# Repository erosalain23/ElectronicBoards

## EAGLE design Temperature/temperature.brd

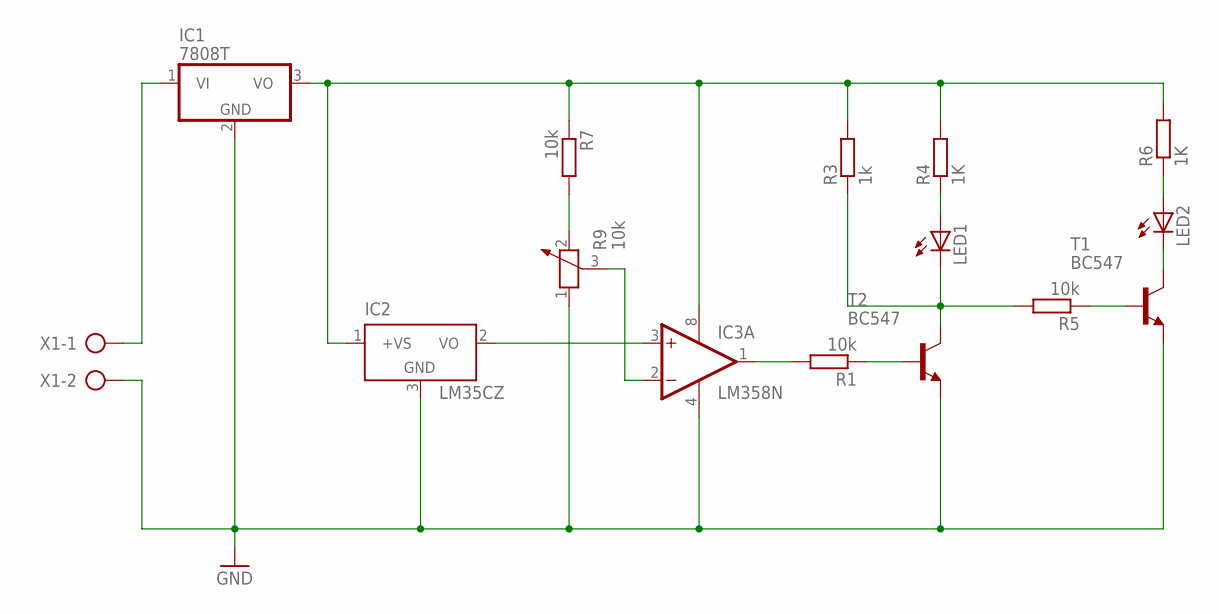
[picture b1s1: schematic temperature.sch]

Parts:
IC1: 7808T; TO220H
IC2: LM35CZ; TO92
IC3: LM358N; DIL08
LED1, LED2: LED5MM
R1, R5, R7: 10k; 0204/7
R3: 1k; 0204/7
R4, R6: 1K; 0204/7
R9: 10k; PT-10
T1, T2: BC547; TO92
X1: AK300/2

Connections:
GND: IC1.2 (GND), IC2.3 (GND), IC3.4 (V-), R9.1, T1.1 (E), T2.1 (E), X1.2
unnamed: IC1.1 (VI), X1.1
unnamed: IC1.3 (VO), IC2.1 (+VS), IC3.8 (V+), R3.2, R4.2, R6.2, R7.1
unnamed: R7.2, R9.2
unnamed: IC2.2 (VO), IC3.3 (+IN)
unnamed: IC3.2 (-IN), R9.3
unnamed: IC3.1 (OUT), R1.2
unnamed: R1.1, T2.2 (B)
unnamed: LED1.K (C), R3.1, R5.2, T2.3 (C)
unnamed: LED1.A, R4.1
unnamed: LED2.K (C), T1.3 (C)
unnamed: LED2.A, R6.1
unnamed: R5.1, T1.2 (B)

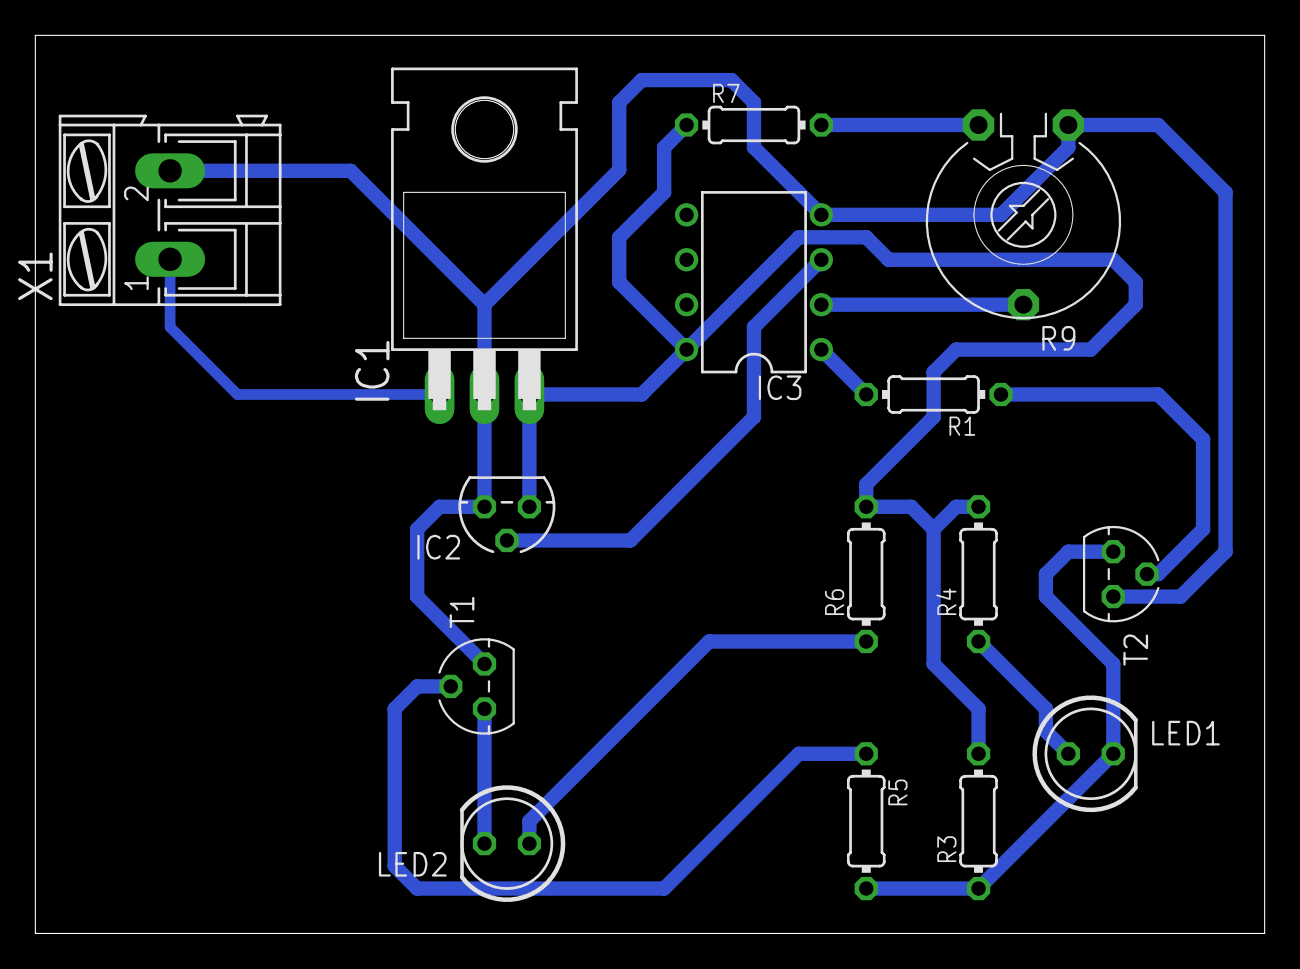
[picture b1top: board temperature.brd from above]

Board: 2 copper layers, 69.5 x 50.8 mm, 15 parts (0 on the bottom side), 13 nets.

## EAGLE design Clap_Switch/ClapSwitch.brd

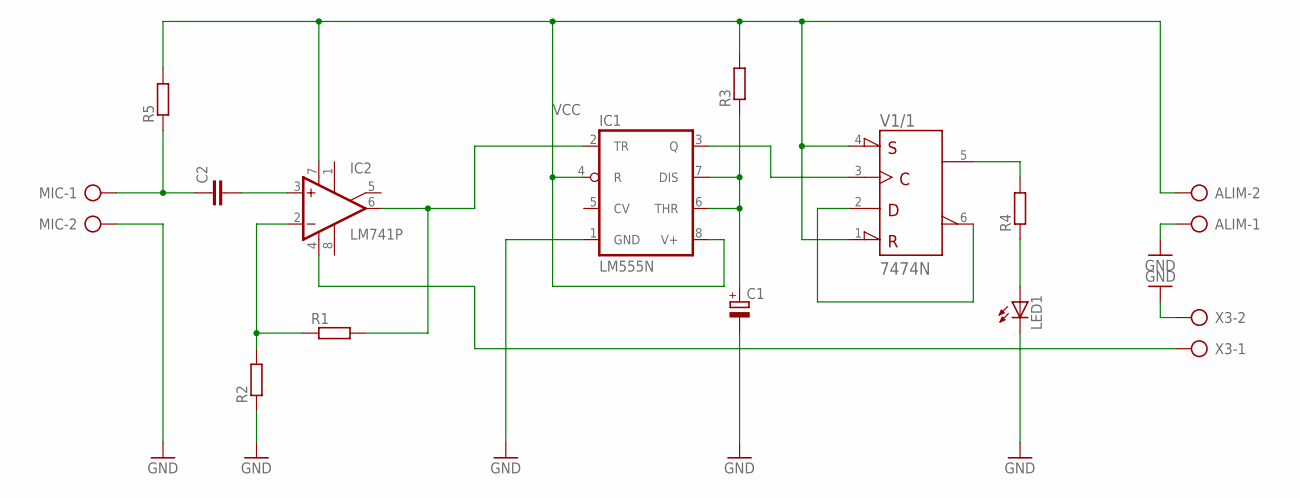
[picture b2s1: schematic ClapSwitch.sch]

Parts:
ALIM: AK300/2
C1: CPOL-EUE5-8.5; E5-8,5
C2: C-EU050-030X075; C050-030X075
IC1: LM555N; DIL08
IC2: LM741P; DIL08
LED1: LEDLZR181; LZR181
MIC: AK300/2
R1, R2, R3, R4, R5: R-EU_0204/7; 0204/7
V1: 7474N; DIL14
X3: AK300/2

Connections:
+UB: V1.14 (+UB)
-UB: V1.7 (-UB)
GND: ALIM.1, C1.-, IC1.1 (GND), LED1.K (C), MIC.2, R2.1, X3.2
unnamed: IC1.3 (Q), V1.3 (CLK)
unnamed: IC2.4 (V-), X3.1
unnamed: V1.2 (D), V1.6 (!Q)
unnamed: R4.2, V1.5 (Q)
unnamed: C1.+, IC1.6 (THR), IC1.7 (DIS), R3.1
unnamed: LED1.A, R4.1
unnamed: C2.1, MIC.1, R5.1
unnamed: IC1.2 (TR), IC2.6 (OUT), R1.2
unnamed: IC2.2 (-IN), R1.1, R2.2
unnamed: C2.2, IC2.3 (+IN)
VCC: ALIM.2, IC1.4 (R), IC1.8 (V+), IC2.7 (V+), R3.2, R5.2, V1.1 (!CLR), V1.4 (!PRE)

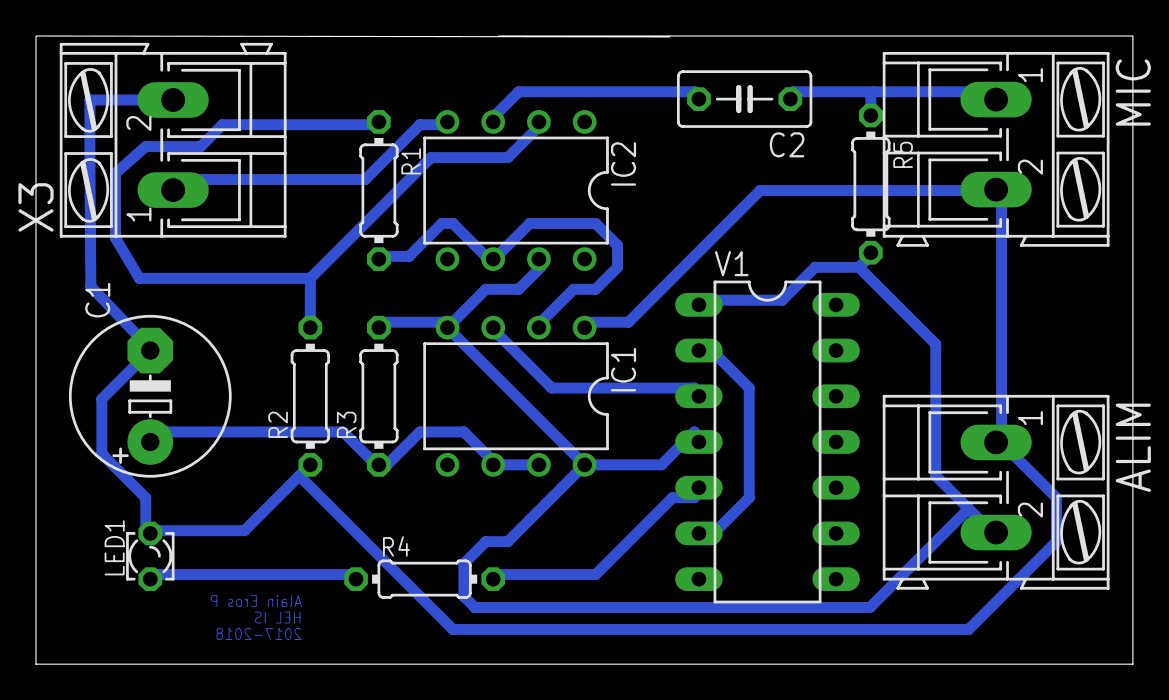
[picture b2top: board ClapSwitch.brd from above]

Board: 2 copper layers, 60.9 x 34.9 mm, 14 parts (0 on the bottom side), 12 nets.

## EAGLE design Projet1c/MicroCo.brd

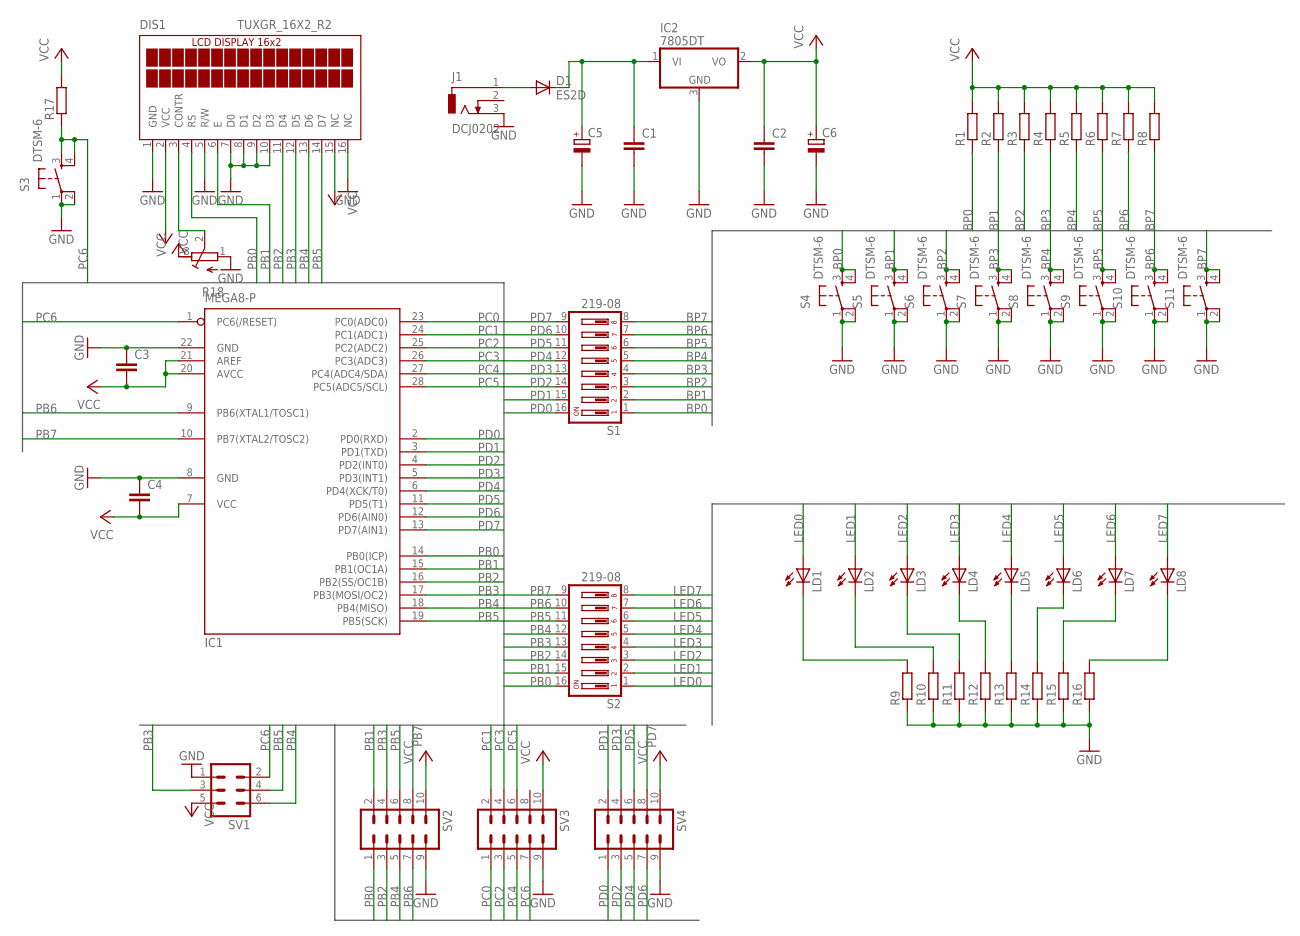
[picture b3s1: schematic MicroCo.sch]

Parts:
C1, C2, C3, C4: C-EUC1206; C1206
C5: CPOL-EU153CLV-1010; 153CLV-1010
C6: CPOL-EU153CLV-0605; 153CLV-0605
D1: ES2D; SMB
DIS1: TUXGR_16X2_R2
IC1: MEGA8-P; DIL28-3
IC2: 7805DT; TO252
J1: DCJ0202
LD1, LD2, LD3, LD4, LD5, LD6, LD7, LD8: LEDCHIPLED_1206; CHIPLED_1206
R1, R2, R3, R4, R5, R6, R7, R8, R9, R10, R11, R12, R13, R14, R15, R16, R17: R-EU_M1206; M1206
R18: R-TRIMM4G/J; RTRIM4G/J
S1, S2: 219-08; CTS-219-08
S3, S4, S5, S6, S7, S8, S9, S10, S11: DTSM-6
SV1: ML6
SV2, SV3, SV4: MA05-2

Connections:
BP0: R1.1, S1.1, S4.3, S4.4
BP1: R2.1, S1.2, S5.3, S5.4
BP2: R3.1, S1.3, S6.3, S6.4
BP3: R4.1, S1.4, S7.3, S7.4
BP4: R5.1, S1.5, S8.3, S8.4
BP5: R6.1, S1.6, S9.3, S9.4
BP6: R7.1, S1.7, S10.3, S10.4
BP7: R8.1, S1.8, S11.3, S11.4
GND: C1.2, C2.2, C3.1, C4.1, C5.-, C6.-, DIS1.1 (GND), DIS1.5 (R/W), DIS1.7 (D0), DIS1.8 (D1), DIS1.9 (D2), DIS1.10 (D3), DIS1.16 (NC), IC1.8 (GND), IC1.22 (GND), IC2.3 (GND), J1.3, R9.1, R10.1, R11.1, R12.1, R13.1, R14.1, R15.1, R16.1, R18.1 (A), S3.1, S3.2, S4.1, S4.2, S5.1, S5.2, S6.1, S6.2, S7.1, S7.2, S8.1, S8.2, S9.1, S9.2, S10.1, S10.2, S11.1, S11.2, SV1.1, SV2.9, SV3.9, SV4.9
LED0: LD1.A, S2.1
LED1: LD2.A, S2.2
LED2: LD3.A, S2.3
LED3: LD4.A, S2.4
LED4: LD5.A, S2.5
LED5: LD6.A, S2.6
LED6: LD7.A, S2.7
LED7: LD8.A, S2.8
unnamed: DIS1.3 (CONTR), R18.2 (S)
unnamed: D1.A, J1.1
unnamed: C1.1, C5.+, D1.C, IC2.1 (VI)
unnamed: LD1.C, R9.2
unnamed: LD2.C, R10.2
unnamed: LD3.C, R11.2
unnamed: LD4.C, R12.2
unnamed: LD5.C, R13.2
unnamed: LD6.C, R14.2
unnamed: LD7.C, R15.2
unnamed: LD8.C, R16.2
PB0: DIS1.4 (RS), IC1.14 (PB0(ICP)), S2.16, SV2.1
PB1: DIS1.6 (E), IC1.15 (PB1(OC1A)), S2.15, SV2.2
PB2: DIS1.11 (D4), IC1.16 (PB2(SS/OC1B)), S2.14, SV2.3
PB3: DIS1.12 (D5), IC1.17 (PB3(MOSI/OC2)), S2.13, SV1.3, SV2.4
PB4: DIS1.13 (D6), IC1.18 (PB4(MISO)), S2.12, SV1.6, SV2.5
PB5: DIS1.14 (D7), IC1.19 (PB5(SCK)), S2.11, SV1.4, SV2.6
PB6: IC1.9 (PB6(XTAL1/TOSC1)), S2.10, SV2.7
PB7: IC1.10 (PB7(XTAL2/TOSC2)), S2.9, SV2.8
PC0: IC1.23 (PC0(ADC0)), SV3.1
PC1: IC1.24 (PC1(ADC1)), SV3.2
PC2: IC1.25 (PC2(ADC2)), SV3.3
PC3: IC1.26 (PC3(ADC3)), SV3.4
PC4: IC1.27 (PC4(ADC4/SDA)), SV3.5
PC5: IC1.28 (PC5(ADC5/SCL)), SV3.6
PC6: IC1.1 (PC6(/RESET)), R17.1, S3.3, S3.4, SV1.2, SV3.7
PD0: IC1.2 (PD0(RXD)), S1.16, SV4.1
PD1: IC1.3 (PD1(TXD)), S1.15, SV4.2
PD2: IC1.4 (PD2(INT0)), S1.14, SV4.3
PD3: IC1.5 (PD3(INT1)), S1.13, SV4.4
PD4: IC1.6 (PD4(XCK/T0)), S1.12, SV4.5
PD5: IC1.11 (PD5(T1)), S1.11, SV4.6
PD6: IC1.12 (PD6(AIN0)), S1.10, SV4.7
PD7: IC1.13 (PD7(AIN1)), S1.9, SV4.8
VCC: C2.1, C3.2, C4.2, C6.+, DIS1.2 (VCC), DIS1.15 (NC), IC1.7 (VCC), IC1.20 (AVCC), IC1.21 (AREF), IC2.2 (VO), R1.2, R2.2, R3.2, R4.2, R5.2, R6.2, R7.2, R8.2, R17.2, R18.3 (E), SV1.5, SV2.10, SV3.10, SV4.10

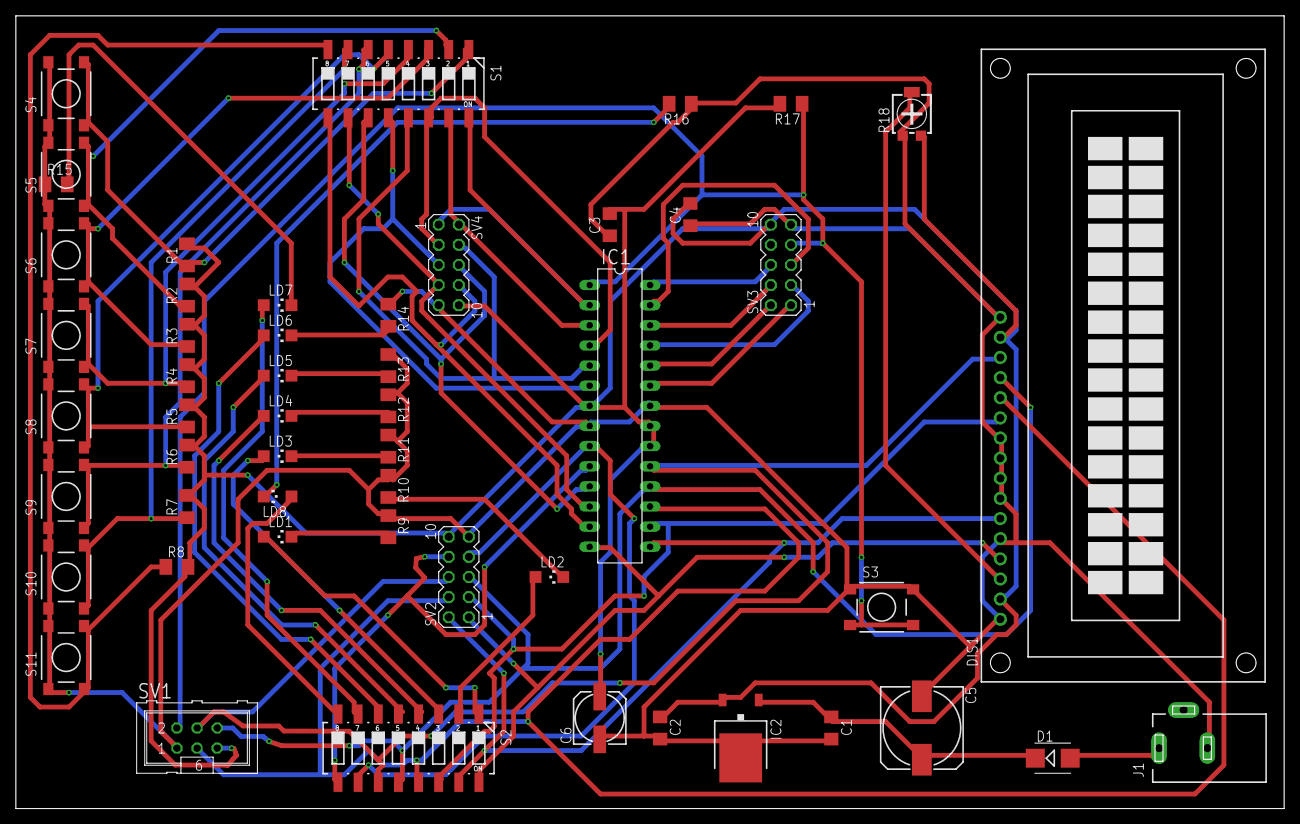
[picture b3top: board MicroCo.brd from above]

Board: 2 copper layers, 160.0 x 100.0 mm, 52 parts (0 on the bottom side), 52 nets.

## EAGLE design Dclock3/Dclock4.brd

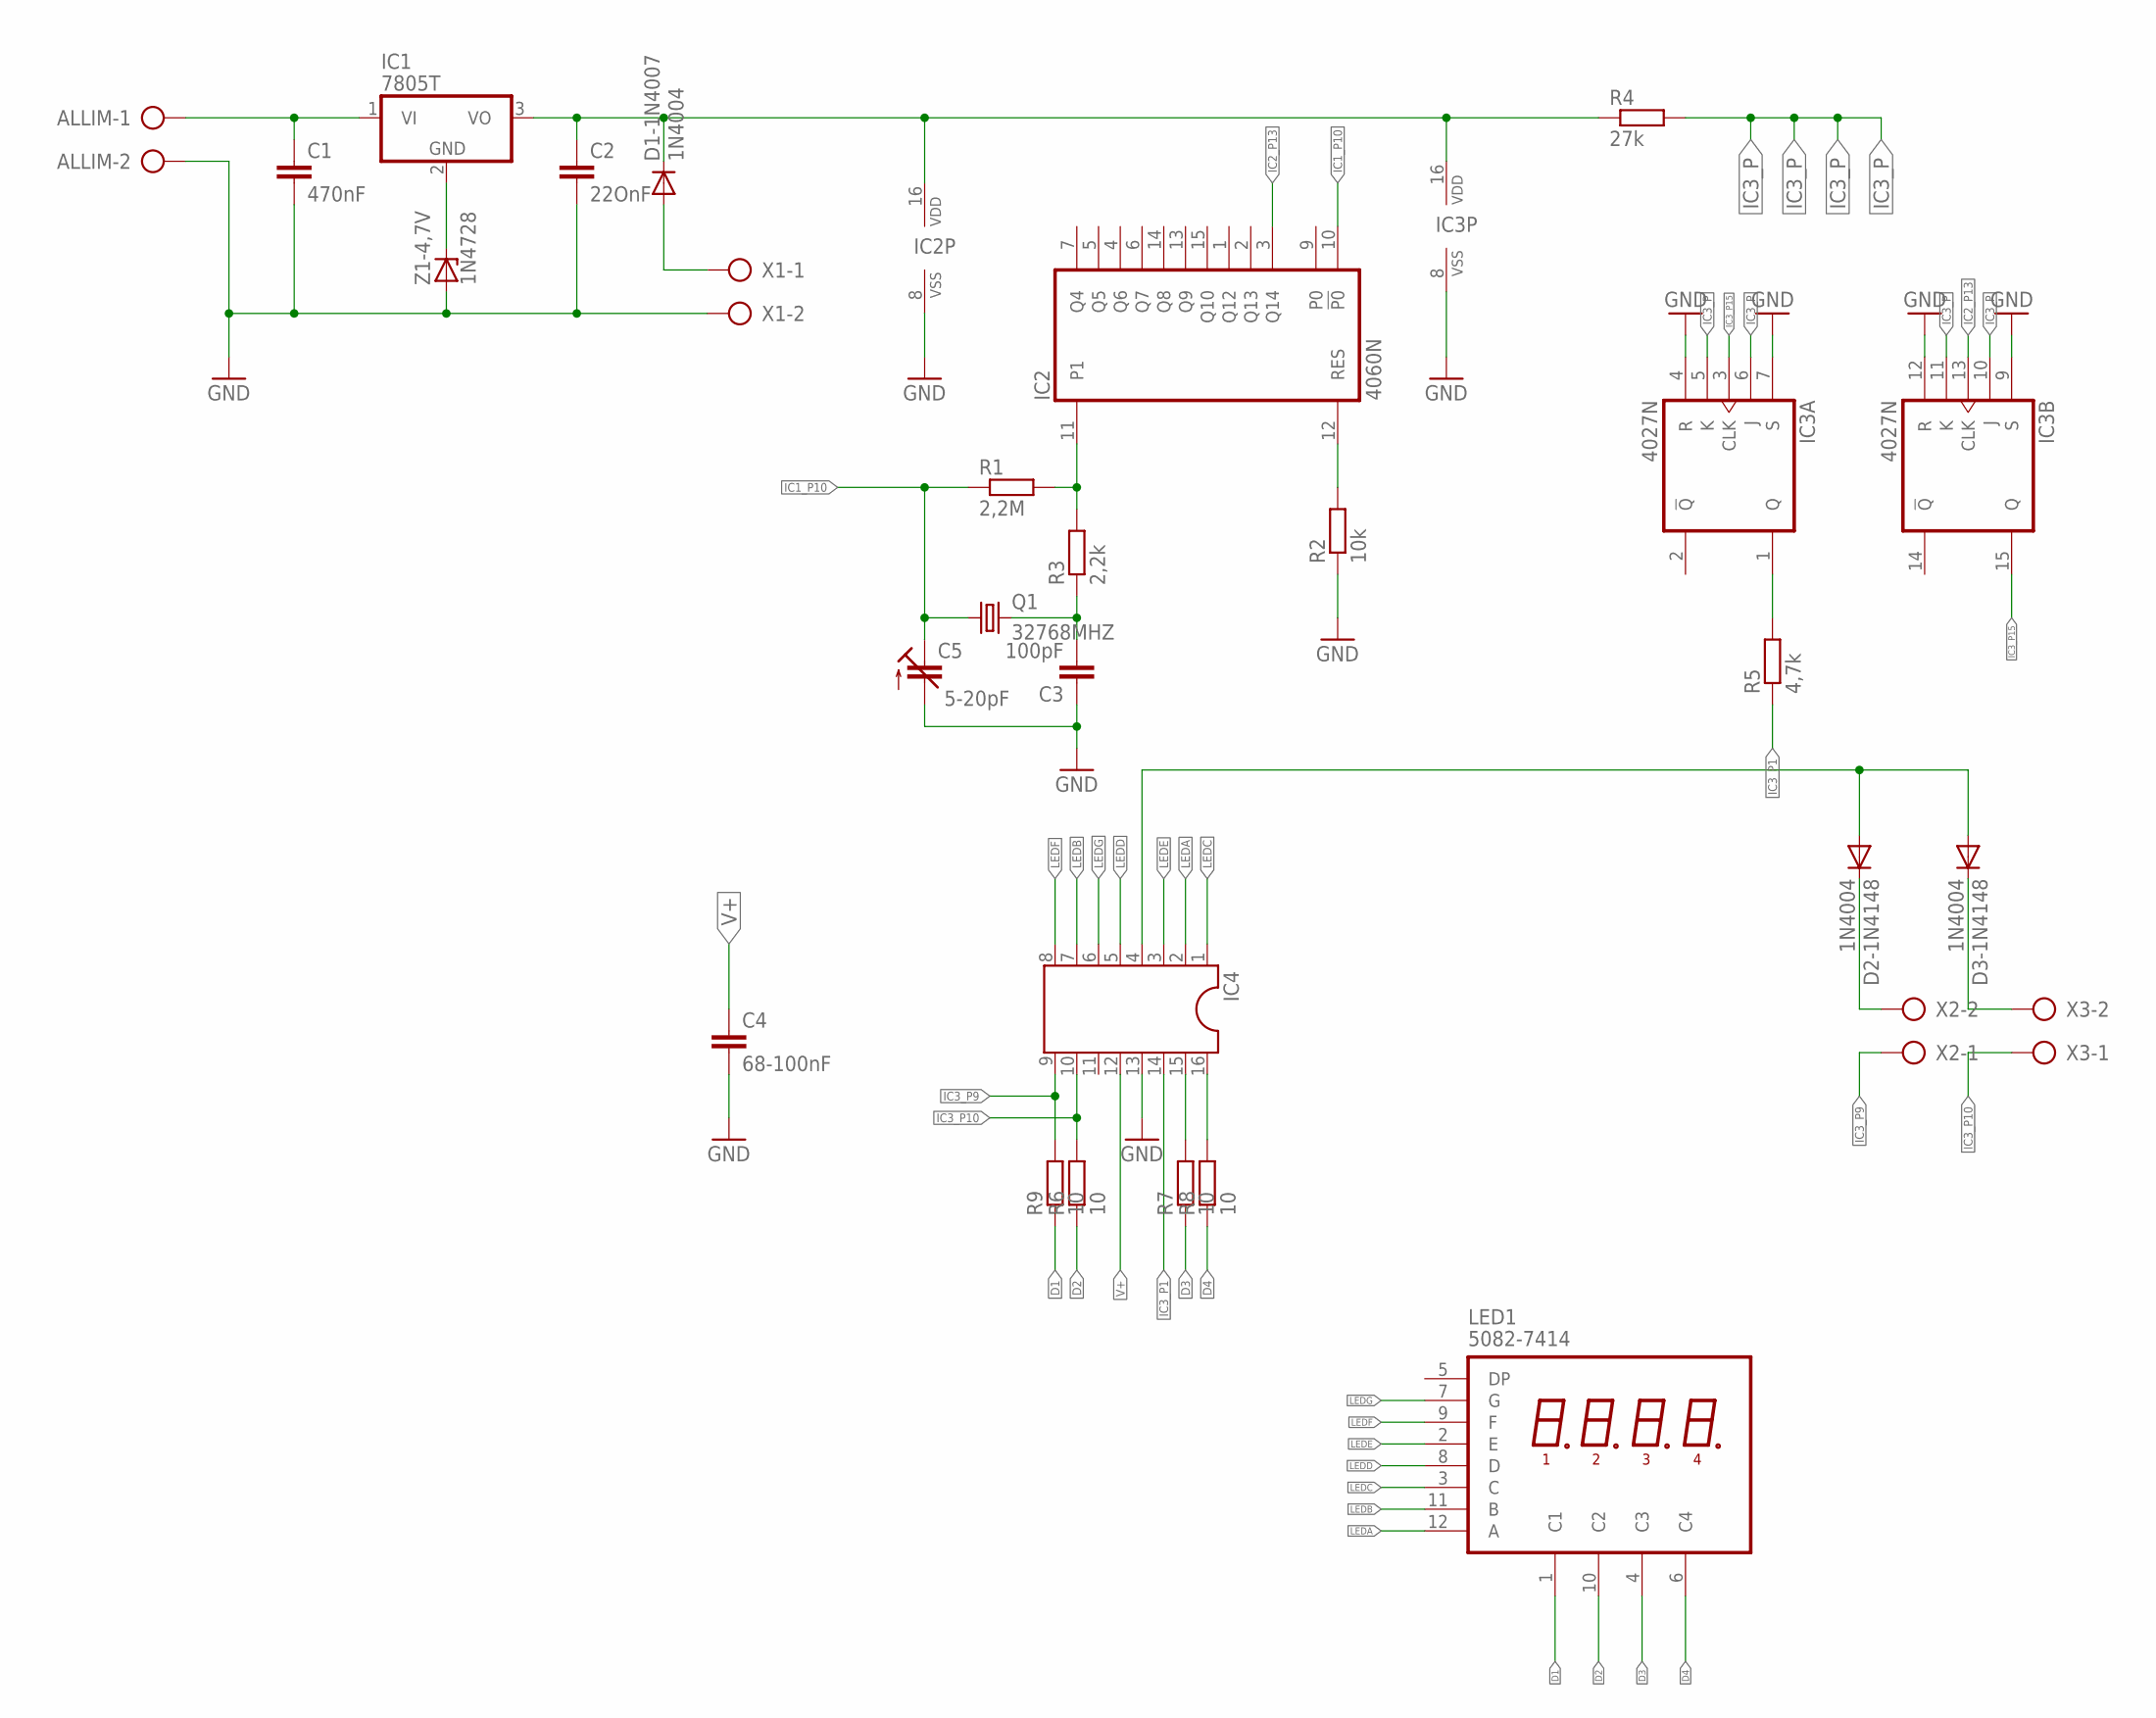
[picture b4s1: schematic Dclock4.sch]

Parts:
ALLIM: AK300/2
C1: 470nF; C050-050X075
C2: 22OnF; C050-050X075
C3: 100pF; C050-050X075
C4: 68-100nF; C050-050X075
C5: 5-20pF; CTRIM808-1
D1-1N4007, D2-1N4148, D3-1N4148: 1N4004; DO41-10
IC1: 7805T; TO220H
IC2: 4060N; DIL16
IC3: 4027N; DIL16
IC4: DIL16
LED1: 5082-7414
Q1: 32768MHZ; HC49/S
R1: 2,2M; 0204/7
R2: 10k; 0204/7
R3: 2,2k; 0204/7
R4: 27k; 0204/7
R5: 4,7k; 0204/7
R6, R7, R8, R9: 10; 0204/7
X1, X2, X3: AK300/2
Z1-4,7V: 1N4728; DO41Z10

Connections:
D1: LED1.1 (C1), R9.1
D2: LED1.10 (C2), R6.1
D3: LED1.4 (C3), R7.1
D4: LED1.6 (C4), R8.1
GND: ALLIM.2, C1.2, C2.2, C3.1, C4.2, C5.2 (A), IC2.8 (VSS), IC3.4 (R), IC3.7 (S), IC3.8 (VSS), IC3.9 (S), IC3.12 (R), IC4.13, R2.1, X1.2, Z1-4,7V.A
IC1_P10: C5.1 (E), IC2.10 (!P0), Q1.1, R1.1
IC2_P13: IC2.3 (Q14), IC3.13 (CLK)
IC3_P: IC3.5 (K), IC3.6 (J), IC3.10 (J), IC3.11 (K), R4.2
IC3_P1: IC4.14, R5.1
IC3_P9: IC4.9, R9.2, X2.1
IC3_P10: IC4.10, R6.2, X3.1
IC3_P15: IC3.3 (CLK), IC3.15 (Q)
LEDA: IC4.2, LED1.12 (A)
LEDB: IC4.7, LED1.11 (B)
LEDC: IC4.1, LED1.3 (C)
LEDD: IC4.5, LED1.8 (D)
LEDE: IC4.3, LED1.2 (E)
LEDF: IC4.8, LED1.9 (F)
LEDG: IC4.6, LED1.7 (G)
unnamed: IC3.1 (Q), R5.2
unnamed: D2-1N4148.A, D3-1N4148.A, IC4.4
unnamed: D2-1N4148.C, X2.2
unnamed: D3-1N4148.C, X3.2
unnamed: ALLIM.1, C1.1, IC1.1 (VI)
unnamed: IC1.2 (GND), Z1-4,7V.C
unnamed: C2.1, D1-1N4007.C, IC1.3 (VO), IC2.16 (VDD), IC3.16 (VDD), R4.1
unnamed: D1-1N4007.A, X1.1
unnamed: IC4.16, R8.2
unnamed: IC4.15, R7.2
unnamed: IC2.12 (RES), R2.2
unnamed: IC2.11 (P1), R1.2, R3.2
unnamed: C3.2, Q1.2, R3.1
V+: C4.1, IC4.12

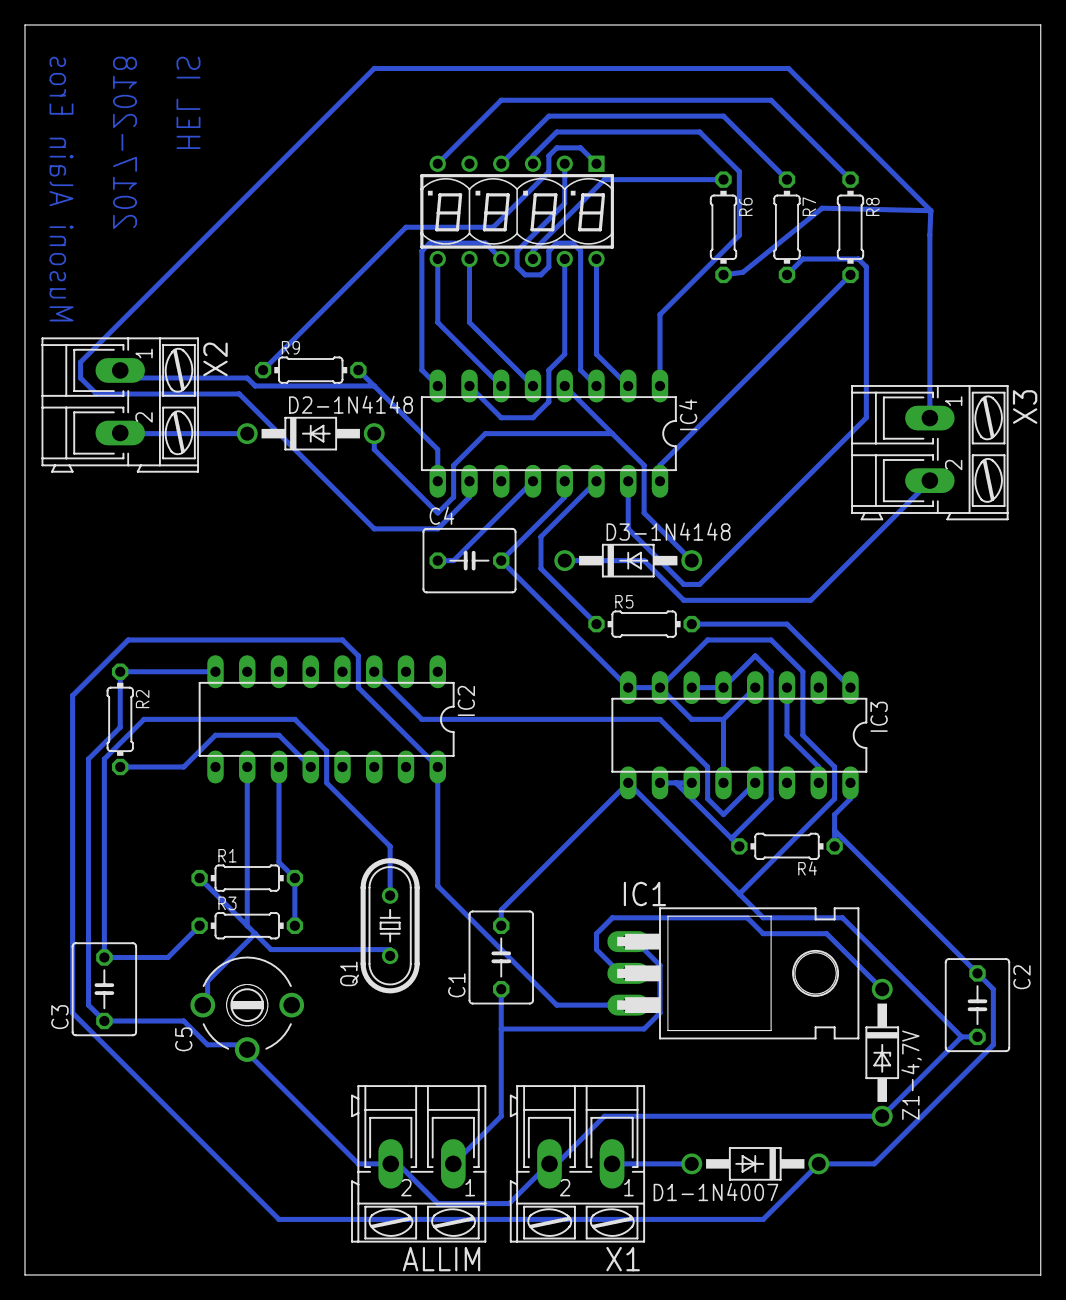
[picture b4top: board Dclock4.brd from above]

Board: 2 copper layers, 81.3 x 100.0 mm, 28 parts (0 on the bottom side), 33 nets.

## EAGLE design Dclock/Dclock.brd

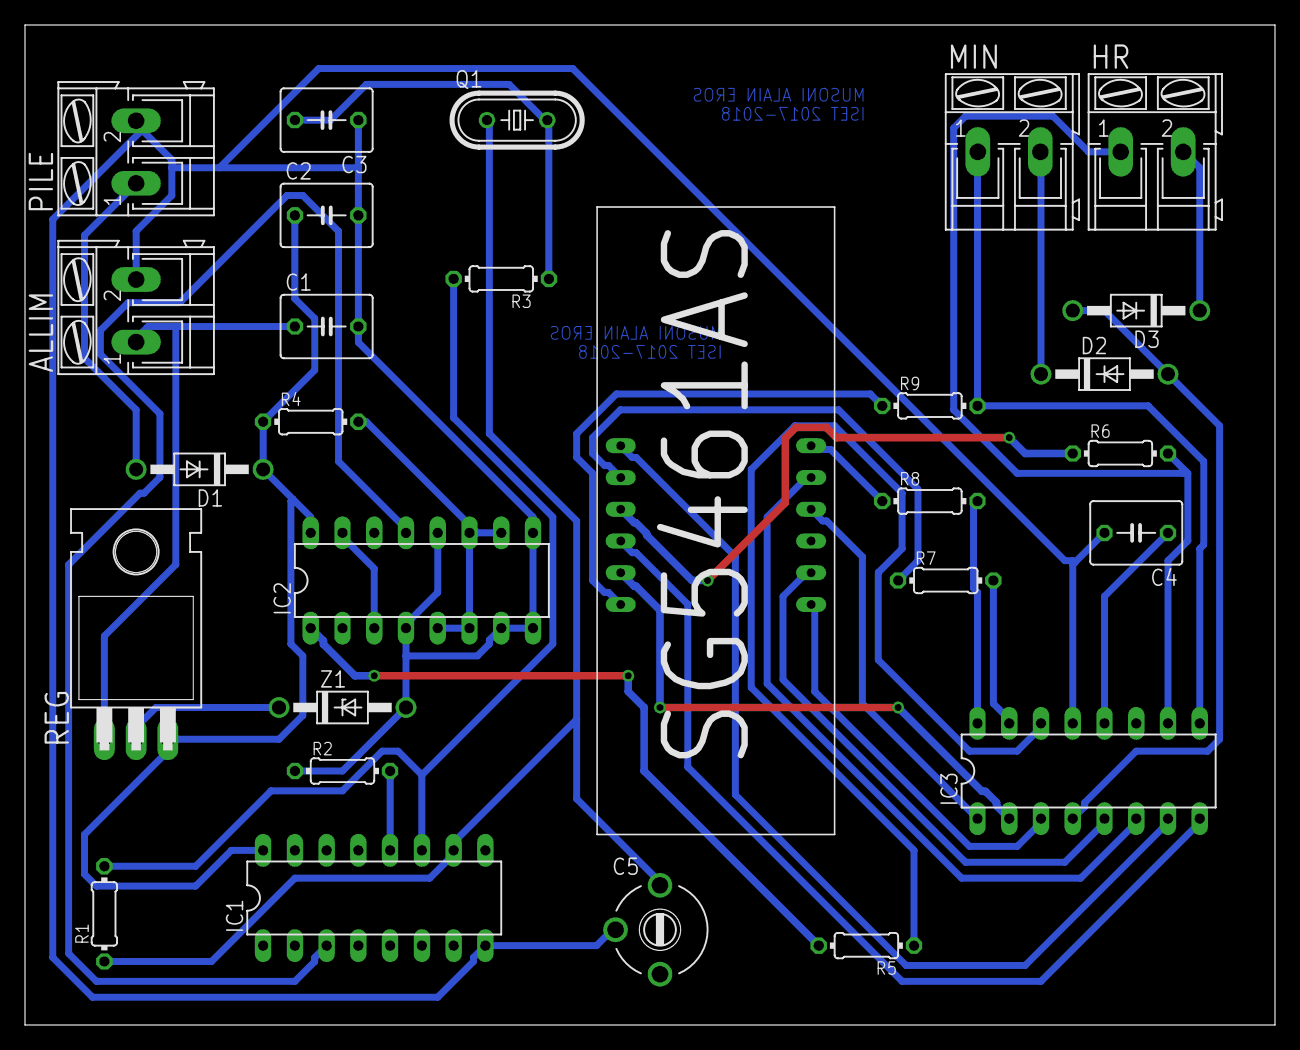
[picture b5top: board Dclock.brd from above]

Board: 2 copper layers, 100.0 x 80.0 mm, 28 parts (0 on the bottom side), 33 nets.

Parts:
ALLIM: AK300/2
C1, C2, C3, C4: C050-050X075
C5: CTRIM808-1
D1, D2, D3: 1N4004; DO41-10
HR: AK300/2
IC1: 4060N; DIL16
IC2: 4027N; DIL16
IC3: DIL16
MIN: AK300/2
PILE: AK300/2
Q1: HC49/S
R1, R2, R3, R4, R5, R6, R7, R8, R9: 0204/7
REG: 7805T; TO220H
U$1: 4DIGIT7SEG12PIN
Z1: 1N4728; DO41Z10

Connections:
D1: R9.1, U$1.P$12
D2: R6.1, U$1.P$9
D3: R7.1, U$1.P$8
D4: R8.1, U$1.P$6
GND: ALLIM.2, C1.2, C2.2, C3.1, C4.2, C5.2, IC1.8, IC2.4, IC2.7, IC2.8, IC2.9, IC2.12, IC3.13, PILE.2, R2.1, Z1.A
IC1_P10: C5.1, IC1.10, Q1.1, R1.1
IC2_P13: IC1.3, IC2.13
IC3_P: IC2.5, IC2.6, IC2.10, IC2.11, R4.2
IC3_P1: IC3.14, R5.1
IC3_P9: IC3.9, MIN.1, R9.2
IC3_P10: HR.1, IC3.10, R6.2
IC3_P15: IC2.3, IC2.15
LEDA: IC3.2, U$1.P$11
LEDB: IC3.7, U$1.P$7
LEDC: IC3.1, U$1.P$4
LEDD: IC3.5, U$1.P$2
LEDE: IC3.3, U$1.P$1
LEDF: IC3.8, U$1.P$10
LEDG: IC3.6, U$1.P$5
unnamed: IC2.1, R5.2
unnamed: D2.A, D3.A, IC3.4
unnamed: D2.C, MIN.2
unnamed: D3.C, HR.2
unnamed: ALLIM.1, C1.1, REG.1
unnamed: REG.2, Z1.C
unnamed: C2.1, D1.C, IC1.16, IC2.16, R4.1, REG.3
unnamed: D1.A, PILE.1
unnamed: IC3.16, R8.2
unnamed: IC3.15, R7.2
unnamed: IC1.12, R2.2
unnamed: IC1.11, R1.2, R3.2
unnamed: C3.2, Q1.2, R3.1
V+: C4.1, IC3.12

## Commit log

2018-06-10 some electronic schematics and boards made during college
